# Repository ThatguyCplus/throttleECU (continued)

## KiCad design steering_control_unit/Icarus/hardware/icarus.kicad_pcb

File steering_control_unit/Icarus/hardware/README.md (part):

# Icarus hardware: schematic rev 0.7 + PCB (rev 0.7 routed, 100 × 100 mm)

The KiCad 10 hierarchical schematic is **generated from code**. Edit `gen/design.py`, then rebuild:

```
cd gen
python make_sch.py
```

Then from `hardware/`:

```
kicad-cli sch erc --severity-all -o erc.rpt icarus.kicad_sch
kicad-cli sch export pdf -o doc/icarus_schematic.pdf icarus.kicad_sch
```

Don't hand-edit the `.kicad_sch` files; the next build overwrites them.

## Status (2026-11-02)

| Check | Result |
|---|---|
| ERC (`--severity-all`) | **0 violations** |
| Netlist vs `design.py` | 292 / 292 nets identical (KiCad netlist export, compared pin by pin) |
| Parts | 567 across 10 sheets (rev 0.5: 22 indicator LEDs, 37 test pads; rev 0.7: TMS570 CH-B) |
| Safety analysis | SPFM 99.99 %, LFM 98.69 %, PMHF 0.095 FIT (placeholder data; `../docs/07_FMEDA_FTA.md`) |
| PCB | **100 × 100 mm**, 4 layers (SGSS), parts on both sides, generated by `gen/make_pcb.py` (config A). DRC: 0 violations, 0 unconnected, 0 schematic-parity issues. See "100 × 100 mm path" |

## Sheets

| Sheet | Contents |
|---|---|
| `power` | Fuse, reverse-battery P-FET, TVS and hold-up. Then **two independent chains**, each LMR38020-Q1 5 V → TPS7B8133-Q1 3.3 V → TPS3702-Q1 5 V window |
| `ch_a` | Control F280049CPZQR, TPS3850-Q1 window watchdog, enable AND gate (GPIO · ERRORSTS · SUP_OK), TCAN3404-Q1, SiT2024B clock, JTAG, UART, LED |
| `ch_b` | Monitor F280049CPZQR (INTOSC), the same supervision, a PWM charge-pump dynamic enable, and the driver-indicator output |
| `overlay` | CH-A analog: 1 MΩ buffered taps, DAC RC slew limit, the Δ authority attenuator (k = 0.109 → ±0.18 V, TBD-DATA), VT6 inverter, summers, readback scaling |
| `guard` | CH-C: buffers, difference amps (D3, D6, sum), window ladder, TLV1704-Q1 comparators, 74LVC1G74 trip latch, self-test and reset FETs |
| `relays` | Two TPS1H100-Q1 high sides, cascaded G6K-2 relays K1/K2, Zener fast-release clamps, CH-B low-side FETs, CH-C guard FET, coil readback |
| `io` | 20-pin vehicle connector (placeholder), CAN ESD and split termination, a separate per-channel divider for every input, VBAT/5V/Vcc2/ground-offset monitors |

## Rev 0.7 changes: diverse monitor MCU (TMS570)

CH-B moves from a second F280049C to a **TMS570LS0432-Q1** (orderable TMS5700432BPZQQ1). It's an Arm Cortex-R4F with dual cores in lockstep, ECC, CPU/RAM self-test and the ESM error pin, in the same 14 × 14 mm LQFP-100. Control (C28x) and monitor (Arm) now share no silicon, compiler or toolchain: `../docs/06_SAFETY_ELEMENT.md` F16.

Every pin comes from the datasheet (SPNS186C Tables 4-1 to 4-16); the generator checks all 100 are assigned exactly once.

| Function | Rev 0.6 (F280049C) | Rev 0.7 (TMS570) |
|---|---|---|
| Link to CH-A | FSI | **UART**: F280049C SCI-B on GPIO12/13 (the same two pins) ⇄ TMS570 SCI (LIN module) on pins 94/95, 470 Ω series each way, CRC + counter in firmware |
| Error pin into the enable gate (SM-03) | ERRORSTS (GPIO24) | **ESM nERROR** (pin 82): low = error, pulled down in reset |
| Expected-Δ reference for the guard (SM-20) | DAC-A | **N2HET[6] PWM** (~100 kHz) into the same 10 k / 1 µF RC (< 1 mV ripple); still read back on REF3M_B. The part has no DAC |
| Clock | INTOSC2 | **16 MHz quartz**, load caps to KELVIN_GND only (Note B); the crystal part is still TBD |
| Core supply | internal VREG | **TLV73312PQDRVRQ1** 1.2 V from +5V0_B (0.55 W worst case), window-supervised by **TPS3702CX12QDDCRQ1** wired into nPORRST with the TPS3850 |
| ADC | 16 of 20+ channels | All **16** MibADC inputs used; VCCAD = ADREFHI = VDDA_B (3.3 V, ferrite-filtered) |
| Debug | ARM 10-pin + UART | **TI cTI-20** JTAG (nTRST pulled down inside: TAP held in reset without a debugger). The pinout still needs checking against the XDS110 guide. No UART: the one SCI is the link |

- **Pinout traps caught:** TLV733P-Q1 has a different pin order in WSON-6 than in SOT-23. KiCad's library symbol is the SOT-23 one, so the WSON-6 symbol is custom.
- **Safety:** SM-25 (lockstep + ESM) added. FMEDA, still on placeholder rates: **SPFM 99.988 %, LFM 98.80 %, PMHF 0.086 FIT** (was 0.096). Parity: ERC 0, netlist 292 / 292.
- **Cost of the change:** CH-B firmware is now a separate HALCoGen / TI Arm codebase. That's the point of diversity, but it doubles the firmware effort.

## Rev 0.5 changes: indicator LEDs (22 in total, all 0603)

| Where | LED | Lit when | Drive |
|---|---|---|---|
| `power` | 5 × green | VBAT_P, +5V0_A_SRC (buck A), +5V0_B, +3V3_A, +3V3_B present | Rail → R → LED, ~1.4 mA |
| `ch_a` / `ch_b` | green heartbeat (existing, GPIO34 pin 94) | Firmware heartbeat | GPIO |
| | red FAULT (GPIO5, pin 89) | Latched fault / SAFE | GPIO |
| | yellow CAN (GPIO9, pin 90) | Pulsed per CAN frame, stretched to 20 ms | GPIO |
| | orange ENGAGED (A) / PERMISSIVE (B) (GPIO10, pin 93) | Overlay engaged / CH-B grants its low side | GPIO |
| | red SUP (hardware) | Watchdog or 5 V window holds SUP_OK low; works with the MCU in reset | +3V3 → 2.2k → LED → SUP_OK |
| `guard` | red GUARD TRIP | CH-C latch tripped | Latch Q (the coil gate uses Q-bar) |
| `relays` | 2 × blue K1 / K2 | Coil actually energized (high side and both low sides on) | Across the coil, behind a 1N4148WS |
| `backup` | yellow CHG, green DONE, green PG, red LOW CELL | MCP73833 STAT1 / STAT2 / PG, TPS61092 LBO | Open-drain sinks |

- **No LED can work against a safety mechanism.** Each placement choice is argued in `../docs/06_SAFETY_ELEMENT.md` F14. The relay LEDs need the series diode so the ~19 V release flyback can't reverse-break the LED and shunt the fast-release Zener.
- **No LED on VLI or VBK5**, so an idle car doesn't drain the backup cell.
- **Firmware notes.** The coil LEDs add ~0.9 mA to the TPS1H100 current-sense reading. The CAN LED needs pulse stretching to be visible.

## Rev 0.4 changes

- **From the throttle ECU:** TCAN3404-Q1 CAN and TPS3702 window OV/UV supervisors (both already in), SMBJ20A TVS and SQJ147 reverse FET (already in), plus a new **1812 PTC** behind the blade fuse (throttle F1).
- **SM-23, speed-dependent authority.** A CH-C analog speed stage (`guard` sheet) and a TS5A3159-Q1 that halves the overlay command above v_switch (`overlay` sheet). It fails to HALF or zero.
- **1S LiPo backup** (`backup` sheet): JST-PH → PTC → MCP73833 charger (from `+5V0_A_SRC`) → TPS61092 5 V boost → LM66100 ideal diodes into both 5 V rails. Relay coils are not backed up, on purpose.
- **SM-24:** a TPS3702 on the boost output disables both ideal diodes on overvoltage.
- **Caught and fixed during the build:** TS5A3159 COM/NC swap (full authority at high speed), TPS61091 → TPS61092 (3.3 V vs 5 V part), TPS61092 LBO pin unconnected, SN74LVC1G123 footprint (SOT-23-8 → SSOP-8 for the DCT package).

## Rev 0.3 changes (logic review + R3–R5, `../docs/06_SAFETY_ELEMENT.md`)

- **R8, authority limit moved into the summers.** OVL3 = RAW3 + k(DCMD − VMID), OVL6 = RAW6 − k(DCMD − VMID), k = 1.1 k / 10 k = 0.110, four 0.1 % values mirrored. A railed op-amp upstream of a summer is now bounded to 0.37 V (was ~3.3 V). One op-amp quad and the inverter stage removed.
- **R7, 2oo2 guard-latch clear.** SN74LVC1G08-Q1: CH-A GPIO57 (pin 66, via 1 k) AND CH-B GUARD_RST → clear FET.
- **R3, low-side guard test.** Ladder bottom through a normally-on BSS138 (gate pull-up); CH-B GPIO4 (pin 75) pulls it low to lift every threshold.
- **R4,** 100 kΩ VT_SNS→VT_EPS bypass on both lines.
- **R5,** TPS3702 SENSE through 10 k with a test FET to 2.5 V; CH-A GPIO4 (pin 75) / CH-B GPIO8 (pin 74).
- **Datasheet checks:** LDO → TPS7B8233-Q1 (300 mA; IDDIO max 113 mA). VDD (1.2 V) decoupling raised to 2 × 10 µF + 4 × 100 nF (~20 µF, per SPRS945). TPS3702CX50 with SET = VDD (4.80 / 5.20 V). TPS1H100 R_CL = 24.9 k → 99 mA limit, CS load 10 k with a 3V3 clamp. X1: single-ended clock on X1 with X2 open (CH-A); X1 to VSS when unused (CH-B). VDDIO_SW to VDDIO, VSS_SW to VSS. All per the datasheet pin table.

## Rev 0.2 changes (from the safety analysis)

- **R1, J1 re-pinned.** The torque lines now sit in a GND-guarded block (pins 6–11). The old CAN_L-next-to-VT3_SNS single-point fault is gone.
- **R2, guard referenced to CH-B's expected Δ.** New group on the `guard` sheet: CH-B DACA → RC → k attenuator → REF3/REF6, with REF3 read back on ADC pin 6. VMID_B and the window ladder (28k / 3.01k / 4.02k / 3.01k / 28k) now run from +3V3_B.

## Decisions made while drawing

- **Watchdog changed to TPS3850-Q1.** The TPS3851-Q1 listed in the concept is timeout-only, so it can't catch a watchdog serviced too early. With the TPS3850 preset (CWD 10 kΩ to VDD, SET0 = SET1 = 1), the window is 1.85 ms closed and 11 ms timeout. Its SENSE pin also monitors 3.3 V for over- and undervoltage.
- **MCU pin mux** (SPRS945 Table 5-6), the same on both channels:

  | Function | Pins |
  |---|---|
  | CAN-A | GPIO30/31 |
  | FSI TX (to the other channel) | GPIO6/7 |
  | FSI RX | GPIO12/13 |
  | SCI-A | GPIO28/29 |
  | ERRORSTS | GPIO24, into the enable AND gate |
  | eCAP inputs (VSP / NEP) | GPIO16/17 |
  | DAC-A (CH-A only) | pin 23 |

- **Reverse-battery P-FET** follows the TI SLVA139 orientation: drain to battery, source to load. The throttle board's netlist has SQJ147 **source** on the fused battery side. Check that on the throttle design; I haven't changed it.

## Open items before layout

1. **TBD-DATA values** (from the logger): Δmax / k, slew τ, guard thresholds, hold-cap value, EPS input impedance (R4).
2. **Relay.** G6K-2F-Y is a stand-in. Pick an automotive-qualified DPDT with gold contacts, and consider a different vendor for K1 and K2.
3. **Vehicle connector.** Choose the part and keep the rev 0.2 pin order (it is safety-relevant). Then build the Y-harness with Honda connector-B halves.
4. **TPS1H100 current-sense ratio K.** The datasheet text extraction lost the value; confirm it and the 10 k CS load scale (V_CS must stay < 3.3 V at the 99 mA limit; the clamp diode covers overshoot).
5. ~~TPS3702 is not automotive-qualified.~~ **Resolved (rev 0.6):** TPS3702CX50QDDCRQ1 (AEC-Q100), same package and pinout. The earlier "no -Q1 exists" note was wrong.
6. **Charge-pump gate.** By analysis the pump is a peak detector: gate ≈ 3.3 − 0.3 ≈ 3.0 V, fine for a BSS138 at 12 mA. Verify on the bench over temperature.
7. **Test points**, then the PCB: four layers, using the throttle `LAYOUT.md` rules.

## PCB (rev 0.5, superseded by the 100 × 100 mm rev 0.7 board below)

| Item | Value |
|---|---|
| Size | **152 × 115 mm** (rev 0.4: 170 × 126 mm, −18 % area), 4 × M3 mounting holes (GND), all parts top-side |
| Stack-up | F.Cu parts + signals · **In1.Cu solid GND plane (no tracks, enforced by `finish`)** · In2.Cu signals + GND fill · B.Cu signals + GND fill. **Order 1 oz on the inner layers** |
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
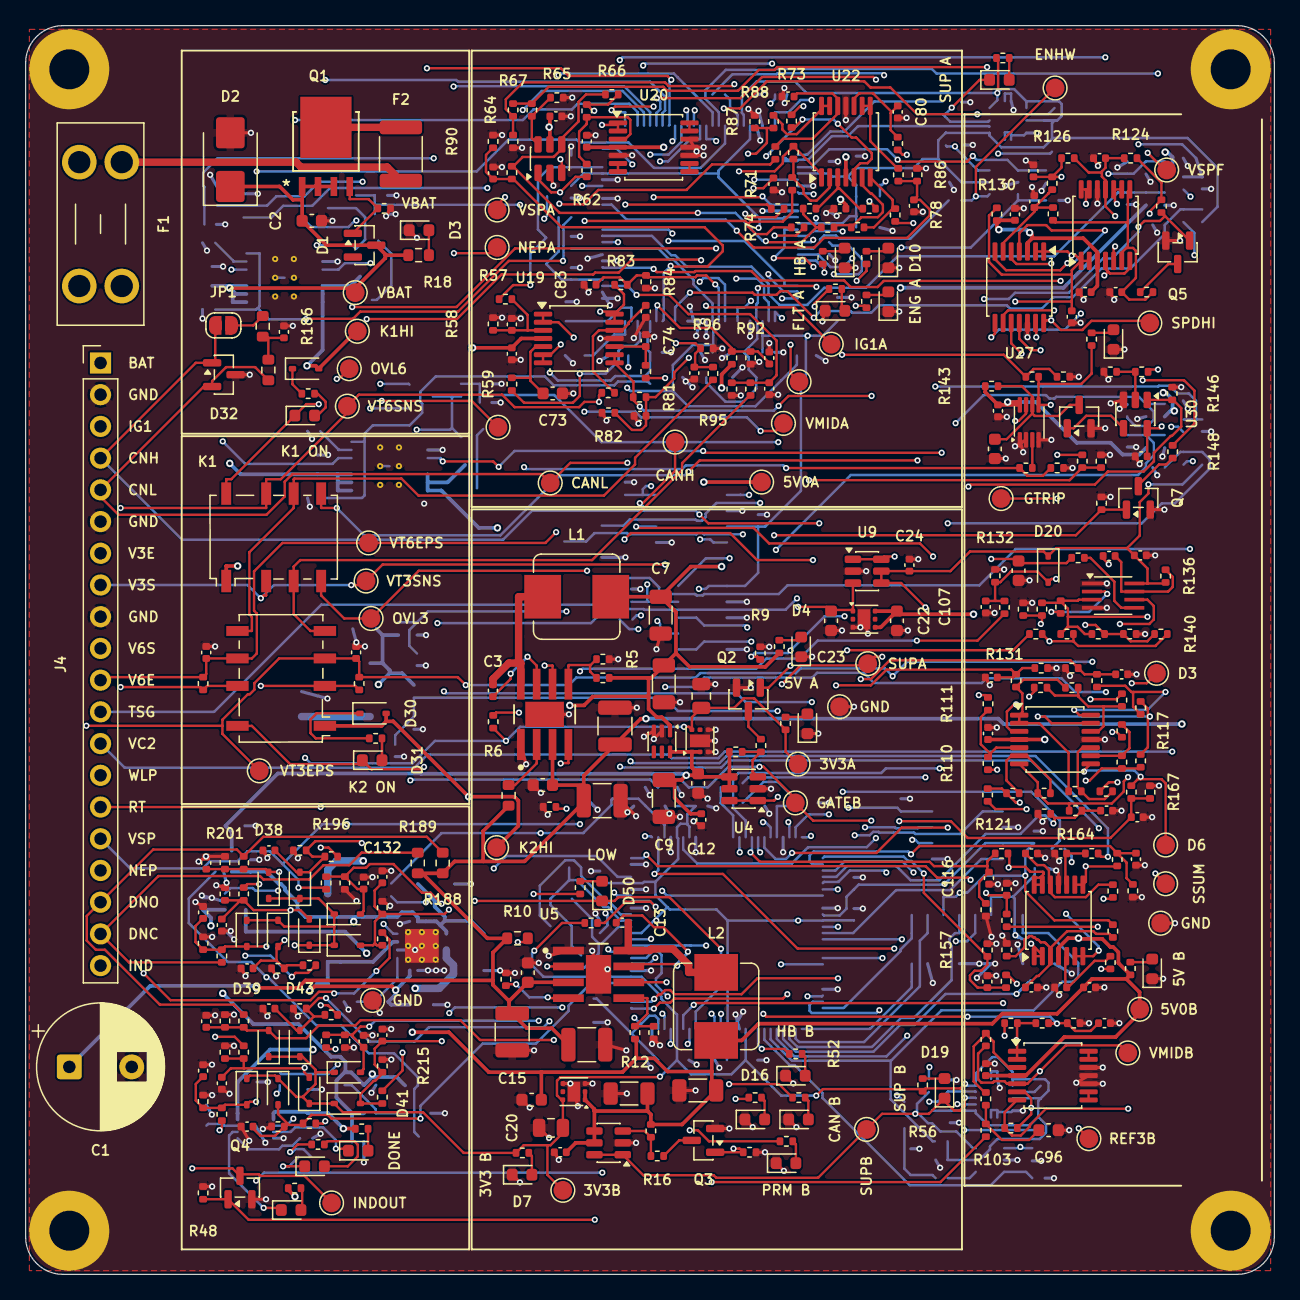
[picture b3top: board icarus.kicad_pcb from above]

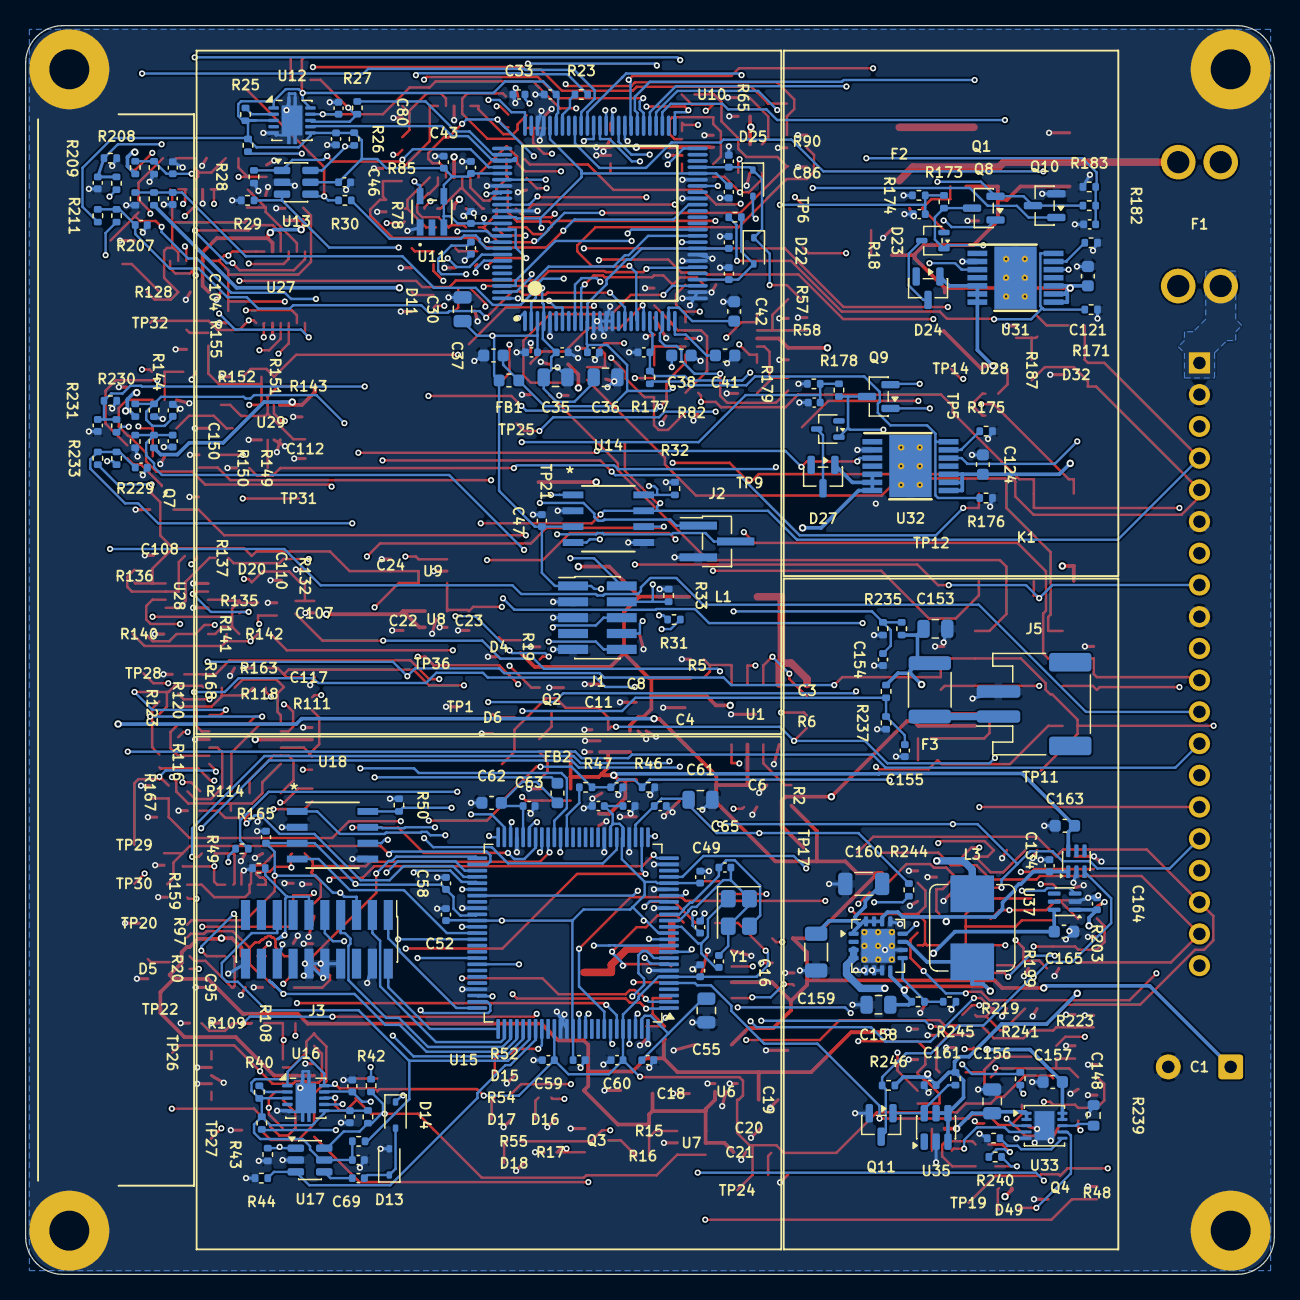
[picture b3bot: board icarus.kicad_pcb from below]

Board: 4 copper layers, 100.0 x 100.0 mm, 571 parts (176 on the bottom side), 292 nets.

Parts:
C1: 470uF 50V; CP_Radial_D10.0mm_P5.00mm
C2, C6, C16: 100nF 100V; C_0603_1608Metric
C3, C12, C13, C21, C24, C25, C26, C27, C28, C29, C31, C32, C33, C34, C39, C40, C43, C45, C46, C47, C48, C49, C50, C51, C52, C53, C54, C56, C57, C58, C59, C60, C63, C67, C68, C69, C70, C71, C72, C76, C77, C78, C79, C90, C95, C97, C99, C104, C105, C108, C109, C111, C113, C140, C141, C151, C152, C154, C155, C161, C162, C164: 100nF; C_0402_1005Metric
C4, C5, C14, C15: 10uF 50V; C_1210_3225Metric
C7, C8, C9, C17, C18, C159, C160: 22uF 16V; C_1206_3216Metric
C10, C19, C37, C38, C41, C42, C62: 2.2uF; C_0603_1608Metric
C11, C20, C30, C35, C36, C55, C61, C153, C156, C158: 10uF; C_0805_2012Metric
C22, C23, C73, C96, C110, C112, C163, C165: 1uF; C_0603_1608Metric
C44, C66, C87, C88, C89, C100, C101, C102, C103, C122, C123, C125, C126, C129, C138, C139, C149, C150: 10nF; C_0402_1005Metric
C64, C65: 12pF; C_0402_1005Metric
C74, C75, C80, C81, C91, C92, C93, C94: 100pF; C_0402_1005Metric
C82, C83, C84, C85, C86, C98, C106, C107, C114, C115, C116, C117, C118, C119, C120, C131, C132, C133, C134, C135, C136, C137, C142, C143, C144, C145, C146, C147, C148: 1nF; C_0402_1005Metric
C121, C124: 100nF 50V; C_0603_1608Metric
C127, C128, C130: 4.7nF; C_0402_1005Metric
C157: 4.7uF; C_0603_1608Metric
D1: BZX84C15; SOT-23
D2: SMBJ20A; D_SMB
D3, D4, D5, D6, D7, D8, D15, D48, D49: LED green; LED_0603_1608Metric
D9, D12, D16, D19, D21, D50: LED red; LED_0603_1608Metric
D10, D17, D47: LED yellow; LED_0603_1608Metric
D11, D18: LED orange; LED_0603_1608Metric
D13, D14: BAT54WS-Q; D_SOD-323
D20, D22, D25, D28, D30, D33, D34, D35, D36, D37, D38, D39, D40, D41, D42, D43, D44, D45, D46: 1N4148WS-Q; D_SOD-323
D23, D26: BAS21-Q; SOT-323_SC-70
D24, D27: BZX84C18; SOT-23
D29, D31: LED blue; LED_0603_1608Metric
D32: ESD2CAN24-Q1; SOT-23
F1: 5A mini blade; Fuseholder_Blade_Mini_Keystone_3568
F2, F3: 1.1A PTC; Fuse_1812_4532Metric
FB1, FB2: 60R@100MHz; L_0603_1608Metric
H1, H2, H3, H4: MountingHole_3.2mm_M3_Pad
J1: JTAG A; PinHeader_2x05_P1.27mm_Vertical_SMD
J2: UART A; PinHeader_1x03_P1.27mm_Vertical_SMD_Pin1Left
J3: JTAG B (TI cTI-20); PinHeader_2x10_P1.27mm_Vertical_SMD
J4: Vehicle harness; PinHeader_1x20_P2.54mm_Vertical
J5: 1S LiPo (JST PH); JST_PH_S2B-PH-SM4-TB_1x02-1MP_P2.00mm_Horizontal
JP1: CAN term; SolderJumper-2_P1.3mm_Open_RoundedPad1.0x1.5mm
K1, K2: G6K-2F-Y 12VDC; Relay_DPDT_Omron_G6K-2F-Y
L1, L2: 10uH; L_Bourns_SRP7028A_7.3x6.6mm
L3: 6.8uH; L_Bourns_SRP7028A_7.3x6.6mm
Q1: SQJ147ELP-T1_GE3; PowerPAK_SO-8L_3_VIS
Q2, Q3, Q4, Q5, Q6, Q7, Q8, Q9, Q10, Q11: BSS138; SOT-23
R1, R7, R8, R15, R16, R25, R26, R32, R40, R41, R45, R47, R50, R57, R58, R59, R81, R83, R85, R87, R89, R91, R92, R97, R98, R103, R105, R108, R130, R134, R135, R139, R141, R151, R153, R156, R158, R160, R162, R164, R166, R168, R171, R176, R184, R185, R205, R206, R207, R227, R228, R229: 10k; R_0402_1005Metric
R2, R10: 100k; R_0603_1608Metric
R3, R11: 64.9k; R_0402_1005Metric
R4, R6, R9, R12, R14, R17, R28, R29, R43, R44, R46, R48, R65, R66, R68, R129, R131, R137, R143, R145, R146, R147, R150, R173, R178, R180, R181, R182, R190, R191, R192, R194, R196, R198, R200, R202, R204, R212, R213, R214, R216, R218, R220, R222, R224, R226, R234, R235, R236, R237, R240, R242, R244, R245, R246: 100k; R_0402_1005Metric
R5, R13, R170, R175: 24.9k; R_0402_1005Metric
R18: 8.2k; R_0603_1608Metric
R19, R20, R24, R33, R38, R39, R51, R56, R155, R247, R248, R249, R250: 2.2k; R_0402_1005Metric
R21, R22, R27, R30, R34, R35, R36, R37, R42, R52, R53, R54, R55, R64, R67, R142, R144, R148, R149, R172, R177, R241: 1k; R_0402_1005Metric
R23: 33; R_0402_1005Metric
R31, R49: 470; R_0402_1005Metric
R60, R61, R79, R80, R93, R95, R99, R100, R101, R102, R140, R208, R209, R210, R211, R230, R231, R232, R233: 1M; R_0402_1005Metric
R62, R63, R69, R71, R73, R75, R106, R107, R110, R111, R112, R113, R114, R115, R116, R117, R118, R119, R120, R121, R122, R123: 10k 0.1%; R_0402_1005Metric
R70, R74: 90.9k 0.1%; R_0402_1005Metric
R72, R76: 1.1k 0.1%; R_0402_1005Metric
R77, R78: 100; R_0402_1005Metric
R82, R84, R86, R88, R90, R109, R152, R154, R157, R159, R161, R163, R165, R167, R169, R243: 20k; R_0402_1005Metric
R94, R96: 2M; R_0402_1005Metric
R104, R138: 82k; R_0402_1005Metric
R124, R128: 28k; R_0402_1005Metric
R125, R127: 3.01k; R_0402_1005Metric
R126: 4.02k; R_0402_1005Metric
R132: 150k; R_0402_1005Metric
R133, R136, R174, R179, R183: 22k; R_0402_1005Metric
R186, R187: 60.4; R_0603_1608Metric
R188, R189: 4.7k; R_0603_1608Metric
R193, R195, R197, R199, R201, R203, R215, R217, R219, R221, R223, R225: 33k; R_0402_1005Metric
R238: 4.7k; R_0402_1005Metric
R239: NTC 10k; R_0603_1608Metric
TP1, TP10, TP20: GND; TestPoint_Pad_D1.5mm
TP2: VBAT_P; TestPoint_Pad_D1.5mm
TP3: IG1_A; TestPoint_Pad_D1.5mm
TP4: VT3_SNS; TestPoint_Pad_D1.5mm
TP5: VT6_SNS; TestPoint_Pad_D1.5mm
TP6: VSP_A; TestPoint_Pad_D1.5mm
TP7: NEP_A; TestPoint_Pad_D1.5mm
TP8: CAN_H; TestPoint_Pad_D1.5mm
TP9: CAN_L; TestPoint_Pad_D1.5mm
TP11: VT3_EPS; TestPoint_Pad_D1.5mm
TP12: VT6_EPS; TestPoint_Pad_D1.5mm
TP13: OVL3_OUT; TestPoint_Pad_D1.5mm
TP14: OVL6_OUT; TestPoint_Pad_D1.5mm
TP15: DCMD_SEL; TestPoint_Pad_D1.5mm
TP16: COIL1_HI; TestPoint_Pad_D1.5mm
TP17: COIL2_HI; TestPoint_Pad_D1.5mm
TP18: GNODE; TestPoint_Pad_D1.5mm
TP19: IND_OUT; TestPoint_Pad_D1.5mm
TP21: +5V0_A; TestPoint_Pad_D1.5mm
TP22: +5V0_B; TestPoint_Pad_D1.5mm
TP23: +3V3_A; TestPoint_Pad_D1.5mm
TP24: +3V3_B; TestPoint_Pad_D1.5mm
TP25: VMID_A; TestPoint_Pad_D1.5mm
TP26: VMID_B; TestPoint_Pad_D1.5mm
TP27: REF3_B; TestPoint_Pad_D1.5mm
TP28: D3; TestPoint_Pad_D1.5mm
TP29: D6; TestPoint_Pad_D1.5mm
TP30: SSUM; TestPoint_Pad_D1.5mm
TP31: GTRIP; TestPoint_Pad_D1.5mm
TP32: SPEED_HI_N; TestPoint_Pad_D1.5mm
TP33: VSPF; TestPoint_Pad_D1.5mm
TP34: EN_A_HW; TestPoint_Pad_D1.5mm
TP35: GATE_B; TestPoint_Pad_D1.5mm
TP36: SUP_OK_A; TestPoint_Pad_D1.5mm
TP37: SUP_OK_B; TestPoint_Pad_D1.5mm
U1, U5: LMR38020-Q1; DDA0008E-IPC_A
U2, U36, U37: LM66100-Q1; SOT-363_SC-70-6
U3, U6: TPS7B8233-Q1; WSON-6-1EP_2x2mm_P0.65mm_EP1x1.6mm
U4, U7, U35: TPS3702CX50; SOT-23-6
U8: TLV73312P-Q1; WSON-6-1EP_2x2mm_P0.65mm_EP1x1.6mm
U9: TPS3702CX12-Q1; SOT-23-6
U10: F280049CPZQR; PZ0100A_M
U11: SiT2024B 10MHz; SOT_SiT1630-S_SIT
U12, U16: TPS3850G33-Q1; VSON-10-1EP_3x3mm_P0.5mm_EP1.65x2.4mm
U13, U17: SN74LVC1G11-Q1; SOT-23-6
U14, U18: TCAN3404-Q1; SOIC8_D_TEX-M
U15: TMS570LS0432-Q1; LQFP-100_14x14mm_P0.5mm
U19, U20, U22, U23, U24, U25: TLV9064-Q1; TSSOP-14_4.4x5mm_P0.65mm
U21: TS5A3159-Q1; SOT-23-6
U26, U27: TLV1704-Q1; TSSOP-14_4.4x5mm_P0.65mm
U28: SN74LVC1G123; SSOP-8_2.95x2.8mm_P0.65mm
U29: SN74LVC1G74-Q1; VSSOP-8_2.3x2mm_P0.5mm
U30: SN74LVC1G08-Q1; SOT-23-5
U31, U32: TPS1H100-Q1; PWP0014F_M
U33: MCP73833; DFN-10-1EP_3x3mm_P0.5mm_EP1.58x2.35mm
U34: TPS61092; Texas_RSA_VQFN-16-1EP_4x4mm_P0.65mm_EP2.7x2.7mm_ThermalVias
Y1: 16MHz; Crystal_SMD_3225-4Pin_3.2x2.5mm

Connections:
+3V3_A: C11.1, C25.1, C26.1, C27.1, C28.1, C29.1, C30.1, C43.1, C45.1, C46.1, C47.1, D22.1, D25.1, D33.1, D34.1, D35.1, D36.1, D37.1, D38.1, D39.1, FB1.1, J1.1, R6.1, R21.1, R24.1, R25.1, R26.1, R38.1, R57.1, R211.2, R240.1, R247.1, TP23.1, U3.6, U10.3, U10.47, U10.70, U10.80, U10.88, U11.3, U11.4, U12.1, U12.3, U12.6, U12.10, U13.5, U14.3
+3V3_B: C20.1, C24.1, C56.1, C57.1, C58.1, C59.1, C60.1, C61.1, C67.1, C68.1, C71.1, C108.1, C113.1, D20.1, D40.1, D41.1, D42.1, D43.1, D44.1, D45.1, D46.1, FB2.1, J3.5, R14.1, R22.1, R39.1, R40.1, R41.1, R45.1, R56.1, R97.1, R124.1, R129.1, R133.1, R135.1, R136.1, R138.1, R141.1, R233.2, R244.1, R250.1, TP24.1, U6.6, U9.4, U9.5, U15.6, U15.28, U15.60, U15.85, U15.96, U16.1, U16.3, U16.6, U16.10, U17.5, U18.3, U28.3, U28.8, U30.5
+5V0_A: C9.1, C10.1, C12.1, C76.1, C77.1, C78.1, C79.1, C163.1, R7.1, R206.1, TP21.1, U2.6, U3.1, U3.2, U4.4, U4.5, U19.4, U20.4, U21.5, U22.4, U36.6
+5V0_A_SRC: C7.1, C8.1, C156.1, L1.2, R4.1, R19.1, R91.1, R248.1, R249.1, U2.1, U33.1, U33.2
+5V0_B: C17.1, C18.1, C19.1, C21.1, C22.1, C95.1, C97.1, C99.1, C104.1, C105.1, C111.1, C165.1, L2.2, R12.1, R15.1, R20.1, R130.1, R143.1, R228.1, TP22.1, U6.1, U6.2, U7.4, U7.5, U8.4, U8.6, U23.4, U24.4, U25.4, U26.3, U27.3, U29.8, U37.6
/backup/BAT_P_IN: F3.1, J5.1
/backup/BKOV_N: Q11.1, R245.2, U35.6
/backup/BK_CE_N: Q11.3, R246.2, U36.3, U37.3
/backup/CHG_DONE_N: D48.1, U33.4
/backup/CHG_PG_N: D49.1, U33.7
/backup/CHG_PROG: R238.1, U33.6
/backup/CHG_STAT: D47.1, R240.2, R241.1, U33.3
/backup/CHG_THERM: R239.1, U33.8
/backup/LBI: R242.2, R243.1, U34.9
/backup/LI_CHG: D47.2, R247.2
/backup/LI_CHGD: D48.2, R248.2
/backup/LI_CHGPG: D49.2, R249.2
/backup/LI_LBO: D50.2, R250.2
/backup/SWB: L3.2, U34.3, U34.4
/ch_a/CAN_RX_A: U10.98, U14.4
/ch_a/CAN_STB_A: R32.1, U10.85, U14.8
/ch_a/CAN_TX_A: U10.99, U14.1
/ch_a/CWD_A: R25.2, U12.2
/ch_a/ENHW_MON_A: R30.2, U10.92
/ch_a/EN_A_GPIO: R28.1, U10.79, U13.1
/ch_a/ERRSTS_A: R29.1, U10.56, U13.3
/ch_a/LEDA_A: D8.2, R34.2
/ch_a/LEDCAN_A: R36.1, U10.90
/ch_a/LEDENG_A: R37.1, U10.93
/ch_a/LEDFLT_A: R35.1, U10.89
/ch_a/LED_A: R34.1, U10.94
/ch_a/LINK_A2B_TX: R31.1, U10.51
/ch_a/LI_CAN_A: D10.2, R36.2
/ch_a/LI_ENG_A: D11.2, R37.2
/ch_a/LI_FLT_A: D9.2, R35.2
/ch_a/LI_SUP_A: D12.2, R38.2
/ch_a/SCI_RX_A: J2.2, U10.1
/ch_a/SCI_TX_A: J2.1, U10.100
/ch_a/SUPOK_MON_A: R27.2, U10.77
/ch_a/TCK_A: J1.4, R33.1, U10.60
/ch_a/TDI_A: J1.8, U10.63
/ch_a/TDO_A: J1.6, U10.61
/ch_a/TMS_A: J1.2, U10.62
/ch_a/WDI_A: U10.78, U12.7
/ch_a/X1_A: R23.2, U10.69
/ch_a/X1_A_S: R23.1, U11.5
/ch_a/XRS_A: C44.1, J1.10, R24.2, U10.2, U12.9
/ch_b/CAN_RX_B: U15.63, U18.4
/ch_b/CAN_STB_B: R50.1, U15.73, U18.8
/ch_b/CAN_TX_B: U15.62, U18.1
/ch_b/CWD_B: R40.2, U16.2
/ch_b/ERRSTS_B: R44.1, U15.82, U17.3
/ch_b/GATE_MON_B: R47.2, U15.39
/ch_b/IND_DRV: Q4.1, R48.1, U15.98
/ch_b/KELVIN_B: C64.2, C65.2, U15.15, Y1.2, Y1.4
/ch_b/LEDA_B: D15.2, R52.2
/ch_b/LEDCAN_B: R54.1, U15.90
/ch_b/LEDFLT_B: R53.1, U15.89
/ch_b/LEDPRM_B: R55.1, U15.97
/ch_b/LED_B: R52.1, U15.83
/ch_b/LINK_B2A_TX: R49.1, U15.95
/ch_b/LI_CAN_B: D17.2, R54.2
/ch_b/LI_FLT_B: D16.2, R53.2
/ch_b/LI_PRM_B: D18.2, R55.2
/ch_b/LI_SUP_B: D19.2, R56.2
/ch_b/NRST_B: J3.15, R45.2, U15.81
/ch_b/OSCIN_B: C64.1, U15.14, Y1.1
/ch_b/OSCOUT_B: C65.1, U15.16, Y1.3
/ch_b/PUMPX_B: C69.2, D13.1, D14.2
/ch_b/PUMP_B: C69.1, U17.4
/ch_b/PWM_EN_B: R43.1, U15.25, U17.1
/ch_b/RTCK_B: J3.9, U15.80
/ch_b/SUPOK_MON_B: R42.2, U15.27
/ch_b/TCK_B: J3.11, R51.1, U15.79
/ch_b/TDI_B: J3.3, U15.77
/ch_b/TDO_B: J3.7, U15.78
/ch_b/TMS_B: J3.1, U15.75
/ch_b/TRST_B: J3.2, U15.76
/ch_b/WDI_B: U15.74, U16.7
/guard/D3N: R112.2, R113.1, U25.6
/guard/D3P: R110.2, R111.2, U25.5
/guard/D6N: R116.2, R117.1, U25.9
/guard/D6P: R114.2, R115.2, U25.10
/guard/DACF_B: C96.1, R103.2, R104.1
/guard/EPS3IN_B: C93.1, R101.2, U23.12
/guard/EPS3_B: R110.1, R118.1, R160.1, U23.13, U23.14
/guard/EPS6IN_B: C94.1, R102.2, U25.3
/guard/EPS6_B: R114.1, R119.1, R162.1, U25.1, U25.2
/guard/GCLR_N: C112.1, Q6.3, R143.2, U29.6
/guard/GRST_2OO2: Q6.1, U30.4
/guard/GUARD_OKQ: R149.1, U29.3
/guard/GUARD_RST_A: R144.2, R145.1, U30.2
/guard/LADB: Q5.3, R128.2
/guard/LI_GTRIP: D21.2, R155.2
/guard/OS_C: C109.1, U28.6
/guard/OS_RC: C109.2, R136.2, U28.7
/guard/RAW3IN_B: C91.1, R99.2, U23.5
/guard/RAW3_B: R112.1, R121.1, R156.1, U23.6, U23.7
/guard/RAW6IN_B: C92.1, R100.2, U23.10
/guard/RAW6_B: R116.1, R122.1, R158.1, U23.8, U23.9
/guard/REF6_B: R107.2, R115.1, U24.7
/guard/REFIN_B: R104.2, R105.1, U24.3
/guard/REFN_B: R106.2, R107.1, U24.6
/guard/SN: R121.2, R122.2, R123.1, U25.13
/guard/SP: R118.2, R119.2, R120.2, U25.12
/guard/SPARE_U24_3: U24.8, U24.9
/guard/SPARE_U24_4: U24.13, U24.14
/guard/SPDREF: R138.2, R139.1, R140.2, U27.9
/guard/SQREF: R133.2, R134.1, U27.10
/guard/TESTD: Q7.3, R148.1
/guard/TH_HD: C100.1, R124.2, R125.1, R148.2, U26.5, U26.11
/guard/TH_HS: C101.1, R125.2, R126.1, U27.5
/guard/TH_LD: C103.1, R127.2, R128.1, U26.6, U26.8
/guard/TH_LS: C102.1, R126.2, R127.1, U27.6
/guard/TRIP_N: C106.1, R130.2, U26.1, U26.2, U26.13, U26.14, U27.1, U27.2, U29.7
/guard/VMIDD_B: C90.1, R97.2, R98.1, U23.3
/guard/VSP_1S: R137.1, U28.5
/guard/VSP_C: C107.1, D20.2, R131.2, R132.1, U27.11
/guard/VSP_SQ: R135.2, U27.13, U28.2
/io/CANH_T: JP1.2, R186.1
/io/CAN_SPLIT: C130.1, R186.2, R187.1
/io/DIS_NC_IN: J4.19, R189.2, R202.1, R224.1
/io/DIS_NO_IN: J4.18, R188.2, R200.1, R222.1
/io/IG1_IN: J4.3, R198.1, R220.1
/io/NEP_IN: J4.17, R192.1, R214.1
/io/RT_IN: J4.15, R196.1, R218.1
/io/TSGND_TAP: J4.12, R210.1, R232.1
/io/VCC2_TAP: J4.13, R208.1, R230.1
/io/WLP_IN: J4.14, R194.1, R216.1
/overlay/DACF_A: C73.1, R59.2, U19.5
/overlay/DCMD_A: R62.1, U19.6, U19.7, U21.1
/overlay/DCMD_HALF: U20.1, U20.2, U21.3
/overlay/DHALFD_A: R62.2, R63.1, U20.3
/overlay/EPS3IN_A: C80.1, R79.2, U22.10
/overlay/EPS3_A: R85.1, U22.8, U22.9
/overlay/EPS6IN_A: C81.1, R80.2, U22.12
/overlay/EPS6_A: R87.1, U22.13, U22.14
/overlay/OVL3: R72.2, R77.1, U22.1
/overlay/OVL6: R76.2, R78.1, U22.7
/overlay/RAW3IN_A: C74.1, R60.2, U19.10
/overlay/RAW3_A: R69.1, R81.1, U19.8, U19.9
/overlay/RAW6IN_A: C75.1, R61.2, U19.12
/overlay/RAW6_A: R73.1, R83.1, U19.13, U19.14
/overlay/SPARE_U20_2: U20.6, U20.7
/overlay/SPARE_U20_3: U20.8, U20.9
/overlay/SPARE_U20_4: U20.13, U20.14
/overlay/SPDSW_IN: R64.2, R65.1, U21.6
/overlay/SUM3N_A: R71.2, R72.1, U22.2
/overlay/SUM3P_A: R69.2, R70.2, U22.3
/overlay/SUM6N_A: R75.2, R76.1, U22.6
/overlay/SUM6P_A: R73.2, R74.2, U22.5
/overlay/VMIDD_A: C72.1, R57.2, R58.1, U19.3
/power/BOOT_A: C3.1, U1.7
/power/BOOT_B: C13.1, U5.7
/power/EN5_A: R2.2, U1.2
/power/EN5_B: R10.2, U5.2
/power/FB_A: R4.2, R5.1, U1.5
/power/FB_B: R12.2, R13.1, U5.5
/power/LI_3V3A: D6.2, R21.2
/power/LI_3V3B: D7.2, R22.2
/power/LI_5V0A: D4.2, R19.2
/power/LI_5V0B: D5.2, R20.2
/power/LI_VBAT: D3.2, R18.2
/power/QREV_G: D1.1, Q1.4, R1.1
/power/RT_A: R3.1, U1.4
/power/RT_B: R11.1, U5.4
/power/SNS5T_A: Q2.3, R8.2
/power/SNS5T_B: Q3.3, R16.2
/power/SNS5_A: R7.2, R8.1, U4.3
/power/SNS5_B: R15.2, R16.1, U7.3
/power/SW_A: C3.2, L1.1, U1.8
/power/SW_B: C13.2, L2.1, U5.8
/power/VBAT_F: F1.2, F2.1
/power/VBAT_FP: F2.2, Q1.5
/relays/CL1: R170.1, U31.13
/relays/CL2: R175.1, U32.13
/relays/CLMP1: D23.3, D24.3
/relays/CLMP2: D26.3, D27.3
/relays/COIL1_LO: D23.1, D29.1, K1.8, Q8.3, R173.1
/relays/COIL2_LO: D26.1, D31.1, K2.8, Q9.3, R178.1
/relays/CSR1: R171.1, R172.1, U31.14
/relays/CSR2: R176.1, R177.1, U32.14
/relays/LI_K1: D29.2, R184.2
/relays/LI_K1D: D28.1, R184.1
/relays/LI_K2: D31.2, R185.2
/relays/LI_K2D: D30.1, R185.1
CAN_H: D32.1, J4.4, JP1.1, TP8.1, U14.7, U18.7
CAN_L: D32.2, J4.5, R187.2, TP9.1, U14.6, U18.6
CHG_STAT_A: R241.2, U10.83
COIL1_HI: D24.1, D28.2, K1.1, TP16.1, U31.5, U31.6, U31.7
COIL2_HI: D27.1, D30.2, K2.1, TP17.1, U32.5, U32.6, U32.7
CSK1_A: C122.1, D22.2, R172.2, U10.29
CSK2_A: C125.1, D25.2, R177.2, U10.21
D3: R113.2, R164.1, TP28.1, U25.7, U26.4, U26.7
D3M_B: C118.1, R164.2, R165.1, U15.54
D6: R117.2, R166.1, TP29.1, U25.8, U26.9, U26.10
D6M_B: C119.1, R166.2, R167.1, U15.55
DACA_OUT: R59.1, U10.23
DCMD_SEL: R66.1, R70.1, R75.1, R89.1, TP15.1, U21.4
DELTAM_A: C86.1, R89.2, R90.1, U10.19
DIAG_EN_A: U10.67, U31.12, U32.12
DISNC_A: C137.1, D39.2, R202.2, R203.1, U10.53
DISNC_B: C148.1, D46.2, R224.2, R225.1, U15.9
DISNO_A: C136.1, D38.2, R200.2, R201.1, U10.64
DISNO_B: C147.1, D45.2, R222.2, R223.1, U15.8
EN_A_HW: R30.1, TP34.1, U13.4, U31.3, U32.3
EPS3M_A: C84.1, R85.2, R86.1, U10.41
EPS3M_B: C116.1, R160.2, R161.1, U15.42
EPS6M_A: C85.1, R87.2, R88.1, U10.7
EPS6M_B: C117.1, R162.2, R163.1, U15.49
GATE_B: C70.1, D14.1, Q8.1, Q9.1, R46.1, R47.1, TP35.1
GND: C1.2, C2.2, C4.2, C5.2, C6.2, C7.2, C8.2, C9.2, C10.2, C11.2, C12.2, C14.2, C15.2, C16.2, C17.2, C18.2, C19.2, C20.2, C21.2, C22.2, C23.2, C24.2, C25.2, C26.2, C27.2, C28.2, C29.2, C30.2, C31.2, C32.2, C33.2, C34.2, C35.2, C36.2, C37.2, C38.2, C39.2, C40.2, C41.2, C42.2, C43.2, C44.2, C45.2, C46.2, C47.2, C48.2, C49.2, C50.2, C51.2, C52.2, C53.2, C54.2, C55.2, C56.2, C57.2, C58.2, C59.2, C60.2, C61.2, C62.2, C63.2, C66.2, C67.2, C68.2, C70.2, C71.2, C72.2, C73.2, C74.2, C75.2, C76.2, C77.2, C78.2, C79.2, C80.2, C81.2, C82.2, C83.2, C84.2, C85.2, C86.2, C87.2, C88.2, C89.2, C90.2, C91.2, C92.2, C93.2, C94.2, C95.2, C96.2, C97.2, C98.2, C99.2, C100.2, C101.2, C102.2, C103.2, C104.2, C105.2, C106.2, C107.2, C108.2, C110.2, C111.2, C112.2, C113.2, C114.2, C115.2, C116.2, C117.2, C118.2, C119.2, C120.2, C121.2, C122.2, C123.2, C124.2, C125.2, C126.2, C127.2, C128.2, C129.2, C130.2, C131.2, C132.2, C133.2, C134.2, C135.2, C136.2, C137.2, C138.2, C139.2, C140.2, C141.2, C142.2, C143.2, C144.2, C145.2, C146.2, C147.2, C148.2, C149.2, C150.2, C151.2, C152.2, C153.2, C154.2, C155.2, C156.2, C157.2, C158.2, C159.2, C160.2, C161.2, C162.2, C163.2, C164.2, C165.2, D2.2, D3.1, D4.1, D5.1, D6.1, D7.1, D8.1, D9.1, D10.1, D11.1, D13.2, D15.1, D16.1, D17.1, D18.1, D21.1, D32.3, H1.1, H2.1, H3.1, H4.1, J1.3, J1.5, J1.9, J2.3, J3.4, J3.8, J3.10, J3.12, J3.16, J3.20, J4.2, J4.6, J4.9, J5.2, Q2.2, Q3.2, Q4.2, Q5.2, Q6.2, Q7.2, Q10.2, Q11.2, R1.2, R3.2, R5.2, R9.2, R11.2, R13.2, R17.2, R28.2, R29.2, R32.2, R33.2, R43.2, R44.2, R46.2, R48.2, R50.2, R51.2, R58.2, R65.2, R68.2, R82.2, R84.2, R86.2, R88.2, R90.2, R92.2, R94.2, R96.2, R98.2, R109.2, R132.2, R134.2, R139.2, R145.2, R146.2, R147.2, R150.2, R152.2, R154.2, R157.2, R159.2, R161.2, R163.2, R165.2, R167.2, R169.2, R170.2, R171.2, R174.2, R175.2, R176.2, R179.2, R183.2, R191.2, R193.2, R195.2, R197.2, R199.2, R201.2, R203.2, R205.2, R207.2, R209.2, R213.2, R215.2, R217.2, R219.2, R221.2, R223.2, R225.2, R227.2, R229.2, R231.2, R235.2, R237.2, R238.2, R239.2, R243.2, TP1.1, TP10.1, TP20.1, U1.1, U1.9, U2.2, U2.3, U3.3, U3.4, U3.7, U4.2, U5.1, U5.9, U6.3, U6.4, U6.7, U7.2, U8.3, U8.7, U9.2, U10.5, U10.12, U10.13, U10.14, U10.15, U10.26, U10.27, U10.32, U10.33, U10.42, U10.45, U10.72, U10.73, U10.82, U10.86, U11.1, U12.5, U12.11, U13.2, U14.2, U14.5, U15.7, U15.17, U15.20, U15.24, U15.29, U15.33, U15.47, U15.59, U15.72, U15.86, U15.87, U15.100, U16.5, U16.11, U17.2, U18.2, U18.5, U19.11, U20.5, U20.10, U20.11, U20.12, U21.2, U22.11, U23.11, U24.10, U24.11, U24.12, U25.11, U26.12, U27.12, U28.1, U28.4, U29.1, U29.2, U29.4, U30.3, U31.2, U31.15, U32.2, U32.15, U33.5, U33.11, U34.5, U34.6, U34.7, U34.10, U34.13, U34.17, U35.2, U36.2, U37.2
GNODE: Q8.2, Q9.2, Q10.3, R182.1, TP18.1
GNODEM_B: C129.1, R182.2, R183.1, U15.50
GRSTA_TX: R144.1, U10.66
GTEST_LO_N: Q5.1, R129.2, U15.67
GTRIP: R151.1, R153.1, R155.1, TP31.1, U29.5
GTRIP_A: R151.2, R152.1, U10.91
GTRIP_B: R153.2, R154.1, U15.1
GUARD_GATE: Q10.1, R149.2, R150.1
GUARD_RST: R146.1, U15.64, U30.1
GUARD_TEST: Q7.1, R147.1, U15.11
IG1_A: C135.1, D37.2, R198.2, R199.1, TP3.1, U10.59
IG1_B: C146.1, D44.2, R220.2, R221.1, U15.5
IND_OUT: J4.20, Q4.3, TP19.1
K1ACOM_M: C88.1, R93.2, R94.1, U10.28
K1A_COM: K1.3, K2.4, R93.1
K1BCOM_M: C89.1, R95.2, R96.1, U10.37
K1B_COM: K1.6, K2.5, R95.1
LBO_N: D50.1, R244.2, U15.93, U34.12
LINK_A2B: R31.2, U15.94
LINK_B2A: R49.2, U10.50
LSN1_B: C123.1, R173.2, R174.1, U15.57
LSN2_B: C126.1, R178.2, R179.1, U15.48
NEP_A: C132.1, D34.2, R192.2, R193.1, TP7.1, U10.55
NEP_B: C143.1, D41.2, R214.2, R215.1, U15.22
OVL3_OUT: K1.4, R77.2, TP13.1
OVL6_OUT: K1.5, R78.2, TP14.1
PG5_A: R6.2, U1.6, U10.65
PG5_B: R14.2, U5.6, U15.18
PORRST_B: C66.1, R39.2, U9.1, U9.6, U15.31, U16.9
RAW3M_A: C82.1, R81.2, R82.1, U10.9
RAW3M_B: C114.1, R156.2, R157.1, U15.51
RAW6M_A: C83.1, R83.2, R84.1, U10.10
RAW6M_B: C115.1, R158.2, R159.1, U15.52
REF3M_B: C98.1, R108.2, R109.1, U15.43
REF3_B: R106.1, R108.1, R111.1, TP27.1, U24.1, U24.2
REFPWM_B: R103.1, U15.26
RT_A_IN: C134.1, D36.2, R196.2, R197.1, U10.58
RT_B_IN: C145.1, D43.2, R218.2, R219.1, U15.12
SM_B: C120.1, R168.2, R169.1, U15.56
SPDHI_A: R67.2, R68.1, U10.81
SPDHI_B: R142.2, U15.2
SPEED_HI_N: R64.1, R67.1, R140.1, R141.2, R142.1, TP32.1, U27.14
SSUM: R123.2, R168.1, TP30.1, U25.14, U27.4, U27.7
SUPTEST_A: Q2.1, R9.1, U10.75
SUPTEST_B: Q3.1, R17.1, U15.68
SUP_OK_A: D12.1, R26.2, R27.1, TP36.1, U4.1, U4.6, U12.8, U13.6
SUP_OK_B: D19.1, R41.2, R42.1, TP37.1, U7.1, U7.6, U16.8, U17.6
TSGM_A: C141.1, R210.2, R211.1, U10.17
TSGM_B: C152.1, R232.2, R233.1, U15.44
V5M_A: C139.1, R206.2, R207.1, U10.36
V5M_B: C150.1, R228.2, R229.1, U15.40
V5SM_A: C87.1, R91.2, R92.1, U10.20
VBATM_A: C138.1, R204.2, R205.1, U10.35
VBATM_B: C149.1, R226.2, R227.1, U15.53
VBAT_IN: F1.1, J4.1
VBAT_P: C1.1, C2.1, C4.1, C5.1, C6.1, C14.1, C15.1, C16.1, C121.1, C124.1, D1.3, D2.1, Q1.1, Q1.2, Q1.3, R2.1, R10.1, R18.1, R188.1, R189.1, R204.1, R226.1, TP2.1, U1.3, U5.3, U31.8, U31.9, U31.10, U32.8, U32.9, U32.10
VBK5: C159.1, C160.1, C161.1, C162.1, C164.1, R245.1, R246.1, U34.1, U34.14, U34.15, U34.16, U35.3, U35.4, U35.5, U36.1, U37.1
VCC1V2_B: C23.1, C48.1, C49.1, C50.1, C51.1, C52.1, C53.1, C54.1, C55.1, U8.1, U9.3, U15.13, U15.21, U15.30, U15.32, U15.61, U15.88, U15.99
VCC2M_A: C140.1, R208.2, R209.1, U10.31
VCC2M_B: C151.1, R230.2, R231.1, U15.41
VDD12_A: C31.1, C32.1, C33.1, C34.1, C35.1, C36.1, U10.4, U10.46, U10.71, U10.87
VDDA_A: C37.1, C38.1, C39.1, C40.1, FB1.2, U10.11, U10.34
VDDA_B: C62.1, C63.1, FB2.2, U15.46
VLI: C153.1, C157.1, C158.1, F3.2, L3.1, R234.1, R236.1, R242.1, U33.9, U33.10, U34.8, U34.11
VLIM_A: C154.1, R234.2, R235.1, U10.44
VLIM_B: C155.1, R236.2, R237.1, U15.45
VMID_A: R63.2, R66.2, R71.1, R74.1, TP25.1, U19.1, U19.2
VMID_B: R105.2, R120.1, TP26.1, U23.1, U23.2, U24.5
VREFHI_A_A: C41.1, U10.25
VREFHI_BC_A: C42.1, U10.24
VSPF: C110.1, R137.2, TP33.1, U27.8
VSP_A: C131.1, D33.2, R190.2, R191.1, TP6.1, U10.54
VSP_B: C142.1, D40.2, R212.2, R213.1, U15.19
VSP_IN: J4.16, R131.1, R190.1, R212.1
VT3_EPS: C127.1, J4.7, K2.3, R79.1, R101.1, R180.2, TP11.1
VT3_SNS: J4.8, K1.2, K2.2, R60.1, R99.1, R180.1, TP4.1
VT6_EPS: C128.1, J4.11, K2.6, R80.1, R102.1, R181.2, TP12.1
VT6_SNS: J4.10, K1.7, K2.7, R61.1, R100.1, R181.1, TP5.1
WLP_A: C133.1, D35.2, R194.2, R195.1, U10.57
WLP_B: C144.1, D42.2, R216.2, R217.1, U15.10

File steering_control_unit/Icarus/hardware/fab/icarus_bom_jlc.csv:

Comment,Designator,Footprint,Manufacturer Part,JLCPCB Part #,Quantity
100nF 100V,"C2,C6,C16",C_0603_1608Metric,,,3
100nF,"C3,C12,C13,C21,C24,C25,C26,C27,C28,C29,C31,C32,C33,C34,C39,C40,C43,C45,C46,C47,C48,C49,C50,C51,C52,C53,C54,C56,C57,C58,C59,C60,C63,C67,C68,C69,C70,C71,C72,C76,C77,C78,C79,C90,C95,C97,C99,C104,C105,C108,C109,C111,C113,C140,C141,C151,C152,C154,C155,C161,C162,C164",C_0402_1005Metric,,,62
10uF 50V,"C4,C5,C14,C15",C_1210_3225Metric,,,4
22uF 16V,"C7,C8,C9,C17,C18,C159,C160",C_1206_3216Metric,,,7
2.2uF,"C10,C19,C37,C38,C41,C42,C62",C_0603_1608Metric,,,7
10uF,"C11,C20,C30,C35,C36,C55,C61,C153,C156,C158",C_0805_2012Metric,,,10
1uF,"C22,C23,C73,C96,C110,C112,C163,C165",C_0603_1608Metric,,,8
10nF,"C44,C66,C87,C88,C89,C100,C101,C102,C103,C122,C123,C125,C126,C129,C138,C139,C149,C150",C_0402_1005Metric,,,18
12pF,"C64,C65",C_0402_1005Metric,,,2
100pF,"C74,C75,C80,C81,C91,C92,C93,C94",C_0402_1005Metric,,,8
1nF,"C82,C83,C84,C85,C86,C98,C106,C107,C114,C115,C116,C117,C118,C119,C120,C131,C132,C133,C134,C135,C136,C137,C142,C143,C144,C145,C146,C147,C148",C_0402_1005Metric,,,29
100nF 50V,"C121,C124",C_0603_1608Metric,,,2
4.7nF,"C127,C128,C130",C_0402_1005Metric,,,3
4.7uF,C157,C_0603_1608Metric,,,1
BZX84C15,D1,SOT-23,BZX84C15-Q,,1
SMBJ20A,D2,D_SMB,SMBJ20A-Q,,1
LED green,"D3,D4,D5,D6,D7,D8,D15,D48,D49",LED_0603_1608Metric,,,9
LED red,"D9,D12,D16,D19,D21,D50",LED_0603_1608Metric,,,6
LED yellow,"D10,D17,D47",LED_0603_1608Metric,,,3
LED orange,"D11,D18",LED_0603_1608Metric,,,2
BAT54WS-Q,"D13,D14",D_SOD-323,,,2
1N4148WS-Q,"D20,D22,D25,D28,D30,D33,D34,D35,D36,D37,D38,D39,D40,D41,D42,D43,D44,D45,D46",D_SOD-323,,,19
BAS21-Q,"D23,D26",SOT-323_SC-70,,,2
BZX84C18,"D24,D27",SOT-23,,,2
LED blue,"D29,D31",LED_0603_1608Metric,,,2
ESD2CAN24-Q1,D32,SOT-23,ESD2CAN24DBZRQ1,,1
1.1A PTC,F2,Fuse_1812_4532Metric,SMDH1812B110TF/33,,1
1.1A PTC,F3,Fuse_1812_4532Metric,MINIASMDC110F/16-2,,1
60R@100MHz,"FB1,FB2",L_0603_1608Metric,BLM18AG600SN1D,,2
CAN term,JP1,SolderJumper-2_P1.3mm_Open_RoundedPad1.0x1.5mm,,,1
G6K-2F-Y 12VDC,K1,Relay_DPDT_Omron_G6K-2F-Y,G6K-2F-Y DC12 (automotive equivalent TBD),,1
G6K-2F-Y 12VDC,K2,Relay_DPDT_Omron_G6K-2F-Y,G6K-2F-Y DC12 (consider a second vendor),,1
10uH,"L1,L2",L_Bourns_SRP7028A_7.3x6.6mm,SRP7028A-100M,,2
6.8uH,L3,L_Bourns_SRP7028A_7.3x6.6mm,SRP7028A-6R8M,,1
SQJ147ELP-T1_GE3,Q1,PowerPAK_SO-8L_3_VIS,SQJ147ELP-T1_GE3,,1
BSS138,"Q2,Q3,Q4,Q5,Q6,Q7,Q8,Q9,Q10,Q11",SOT-23,BSS138Q-7-F,,10
10k,"R1,R7,R8,R15,R16,R25,R26,R32,R40,R41,R45,R47,R50,R57,R58,R59,R81,R83,R85,R87,R89,R91,R92,R97,R98,R103,R105,R108,R130,R134,R135,R139,R141,R151,R153,R156,R158,R160,R162,R164,R166,R168,R171,R176,R184,R185,R205,R206,R207,R227,R228,R229",R_0402_1005Metric,,,52
100k,"R2,R10",R_0603_1608Metric,,,2
64.9k,"R3,R11",R_0402_1005Metric,,,2
100k,"R4,R6,R9,R12,R14,R17,R28,R29,R43,R44,R46,R48,R65,R66,R68,R129,R131,R137,R143,R145,R146,R147,R150,R173,R178,R180,R181,R182,R190,R191,R192,R194,R196,R198,R200,R202,R204,R212,R213,R214,R216,R218,R220,R222,R224,R226,R234,R235,R236,R237,R240,R242,R244,R245,R246",R_0402_1005Metric,,,55
24.9k,"R5,R13,R170,R175",R_0402_1005Metric,,,4
8.2k,R18,R_0603_1608Metric,,,1
2.2k,"R19,R20,R24,R33,R38,R39,R51,R56,R155,R247,R248,R249,R250",R_0402_1005Metric,,,13
1k,"R21,R22,R27,R30,R34,R35,R36,R37,R42,R52,R53,R54,R55,R64,R67,R142,R144,R148,R149,R172,R177,R241",R_0402_1005Metric,,,22
33,R23,R_0402_1005Metric,,,1
470,"R31,R49",R_0402_1005Metric,,,2
1M,"R60,R61,R79,R80,R93,R95,R99,R100,R101,R102,R140,R208,R209,R210,R211,R230,R231,R232,R233",R_0402_1005Metric,,,19
10k 0.1%,"R62,R63,R69,R71,R73,R75,R106,R107,R110,R111,R112,R113,R114,R115,R116,R117,R118,R119,R120,R121,R122,R123",R_0402_1005Metric,,,22
90.9k 0.1%,"R70,R74",R_0402_1005Metric,,,2
1.1k 0.1%,"R72,R76",R_0402_1005Metric,,,2
100,"R77,R78",R_0402_1005Metric,,,2
20k,"R82,R84,R86,R88,R90,R109,R152,R154,R157,R159,R161,R163,R165,R167,R169,R243",R_0402_1005Metric,,,16
2M,"R94,R96",R_0402_1005Metric,,,2
82k,"R104,R138",R_0402_1005Metric,,,2
28k,"R124,R128",R_0402_1005Metric,,,2
3.01k,"R125,R127",R_0402_1005Metric,,,2
4.02k,R126,R_0402_1005Metric,,,1
150k,R132,R_0402_1005Metric,,,1
22k,"R133,R136,R174,R179,R183",R_0402_1005Metric,,,5
60.4,"R186,R187",R_0603_1608Metric,,,2
4.7k,"R188,R189",R_0603_1608Metric,,,2
33k,"R193,R195,R197,R199,R201,R203,R215,R217,R219,R221,R223,R225",R_0402_1005Metric,,,12
4.7k,R238,R_0402_1005Metric,,,1
NTC 10k,R239,R_0603_1608Metric,NCU18XH103F6SRB,,1
LMR38020-Q1,"U1,U5",DDA0008E-IPC_A,LMR38020FSQDDARQ1,,2
LM66100-Q1,"U2,U36,U37",SOT-363_SC-70-6,LM66100QDCKRQ1,,3
TPS7B8233-Q1,"U3,U6",WSON-6-1EP_2x2mm_P0.65mm_EP1x1.6mm,TPS7B8233QDRVRQ1,,2
TPS3702CX50,"U4,U7,U35",SOT-23-6,TPS3702CX50QDDCRQ1,,3
TLV73312P-Q1,U8,WSON-6-1EP_2x2mm_P0.65mm_EP1x1.6mm,TLV73312PQDRVRQ1,,1
TPS3702CX12-Q1,U9,SOT-23-6,TPS3702CX12QDDCRQ1,,1
F280049CPZQR,U10,PZ0100A_M,F280049CPZQR,,1
SiT2024B 10MHz,U11,SOT_SiT1630-S_SIT,SIT2024BA-S2-XXE-10.000000E,,1
TPS3850G33-Q1,"U12,U16",VSON-10-1EP_3x3mm_P0.5mm_EP1.65x2.4mm,TPS3850G33QDRCRQ1,,2
SN74LVC1G11-Q1,"U13,U17",SOT-23-6,SN74LVC1G11QDBVRQ1,,2
TCAN3404-Q1,"U14,U18",SOIC8_D_TEX-M,TCAN3404DRQ1,,2
TMS570LS0432-Q1,U15,LQFP-100_14x14mm_P0.5mm,TMS5700432BPZQQ1,,1
TLV9064-Q1,"U19,U20,U22,U23,U24,U25",TSSOP-14_4.4x5mm_P0.65mm,TLV9064QPWRQ1,,6
TS5A3159-Q1,U21,SOT-23-6,TS5A3159QDBVRQ1,,1
TLV1704-Q1,"U26,U27",TSSOP-14_4.4x5mm_P0.65mm,TLV1704AQPWRQ1,,2
SN74LVC1G123,U28,SSOP-8_2.95x2.8mm_P0.65mm,SN74LVC1G123DCTR,,1
SN74LVC1G74-Q1,U29,VSSOP-8_2.3x2mm_P0.5mm,SN74LVC1G74QDCURQ1,,1
SN74LVC1G08-Q1,U30,SOT-23-5,SN74LVC1G08QDBVRQ1,,1
TPS1H100-Q1,"U31,U32",PWP0014F_M,TPS1H100BQPWPRQ1,,2
MCP73833,U33,DFN-10-1EP_3x3mm_P0.5mm_EP1.58x2.35mm,MCP73833T-AMI/MF,,1
TPS61092,U34,Texas_RSA_VQFN-16-1EP_4x4mm_P0.65mm_EP2.7x2.7mm_ThermalVias,TPS61092RSAR,,1
16MHz,Y1,Crystal_SMD_3225-4Pin_3.2x2.5mm,,,1
